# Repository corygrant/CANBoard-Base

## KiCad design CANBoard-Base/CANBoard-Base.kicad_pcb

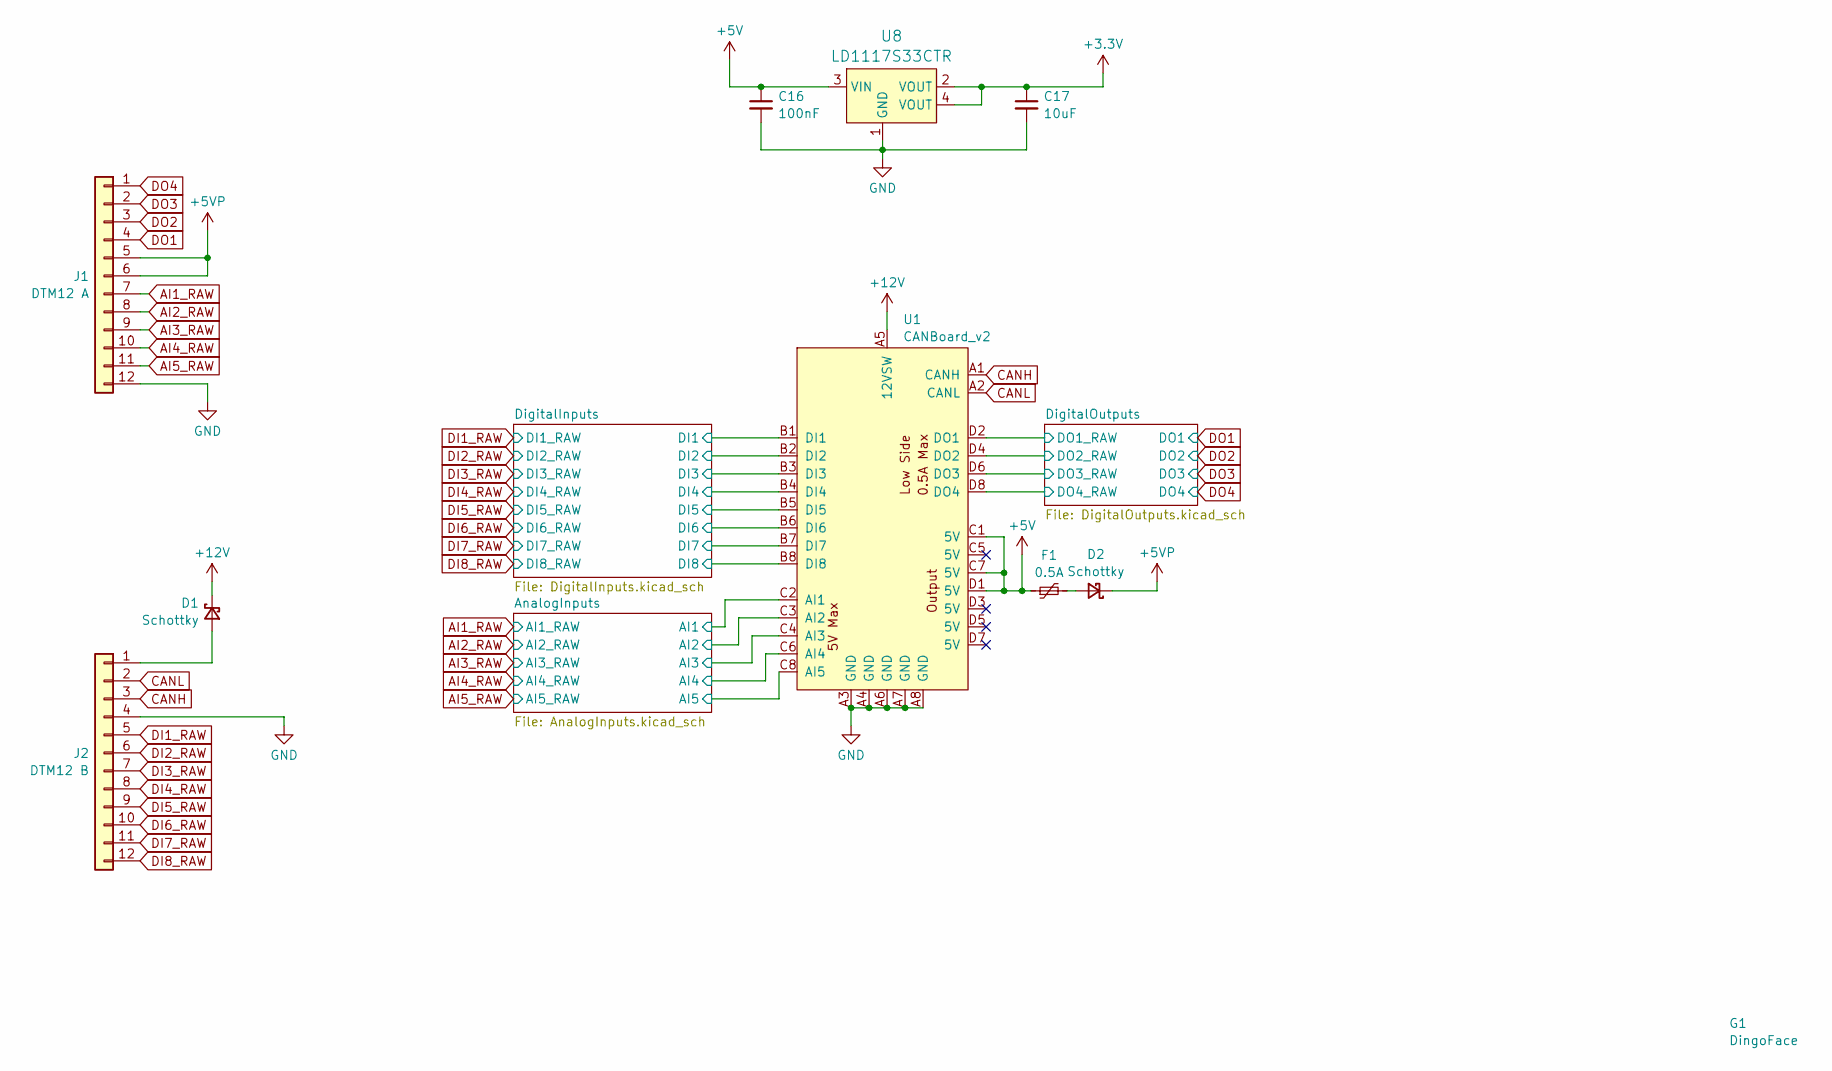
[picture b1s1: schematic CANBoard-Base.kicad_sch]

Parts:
C16: 100nF; C_0805_2012Metric; JLC_PN C49678
C17: 10uF; C_0805_2012Metric; JLC_PN C15850
D1, D2: Schottky; D_SOD-123; JLC_PN C179426
F1: 0.5A; Fuse_0805_2012Metric; JLC_PN C22378359
G1: DingoFace; DingoFaceNoFill
J1: DTM12 A; TE_DTM15-12Px_NoScrewHoles
J2: DTM12 B; TE_DTM15-12Px_NoScrewHoles
U1: CANBoard_v2; CANBoard_v2_NoMountingHoles_TagConnectHoles
U8: LD1117S33CTR; SOT-223; MPN LD1117S33CTR; Digi-Key_PN 497-1241-1-ND

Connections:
+3.3V: C17.1, U8.2 (VOUT), U8.4 (VOUT); also elsewhere on the board
+5V: C16.1, F1.1, U1.C1 (5V), U1.C7 (5V), U1.D1 (5V), U8.3 (VIN); also elsewhere on the board
+5VP: D2.1 (K), J1.5, J1.6
+12V: D1.1 (K), U1.A5 (12VSW); also elsewhere on the board
/AnalogInputs/AI1: U1.C2 (AI1); also elsewhere on the board
/AnalogInputs/AI2: U1.C3 (AI2); also elsewhere on the board
/AnalogInputs/AI3: U1.C4 (AI3); also elsewhere on the board
/AnalogInputs/AI4: U1.C6 (AI4); also elsewhere on the board
/AnalogInputs/AI5: U1.C8 (AI5); also elsewhere on the board
/DigitalInputs/DI1: U1.B1 (DI1); also elsewhere on the board
/DigitalInputs/DI2: U1.B2 (DI2); also elsewhere on the board
/DigitalInputs/DI3: U1.B3 (DI3); also elsewhere on the board
/DigitalInputs/DI4: U1.B4 (DI4); also elsewhere on the board
/DigitalInputs/DI5: U1.B5 (DI5); also elsewhere on the board
/DigitalInputs/DI6: U1.B6 (DI6); also elsewhere on the board
/DigitalInputs/DI7: U1.B7 (DI7); also elsewhere on the board
/DigitalInputs/DI8: U1.B8 (DI8); also elsewhere on the board
/DigitalOutputs/DO1_RAW: U1.D2 (DO1); also elsewhere on the board
/DigitalOutputs/DO2_RAW: U1.D4 (DO2); also elsewhere on the board
/DigitalOutputs/DO3_RAW: U1.D6 (DO3); also elsewhere on the board
/DigitalOutputs/DO4_RAW: U1.D8 (DO4); also elsewhere on the board
AI1_RAW: J1.7; also elsewhere on the board
AI2_RAW: J1.8; also elsewhere on the board
AI3_RAW: J1.9; also elsewhere on the board
AI4_RAW: J1.10; also elsewhere on the board
AI5_RAW: J1.11; also elsewhere on the board
CANH: J2.3, U1.A1 (CANH)
CANL: J2.2, U1.A2 (CANL)
DI1_RAW: J2.5; also elsewhere on the board
DI2_RAW: J2.6; also elsewhere on the board
DI3_RAW: J2.7; also elsewhere on the board
DI4_RAW: J2.8; also elsewhere on the board
DI5_RAW: J2.9; also elsewhere on the board
DI6_RAW: J2.10; also elsewhere on the board
DI7_RAW: J2.11; also elsewhere on the board
DI8_RAW: J2.12; also elsewhere on the board
DO1: J1.4; also elsewhere on the board
DO2: J1.3; also elsewhere on the board
DO3: J1.2; also elsewhere on the board
DO4: J1.1; also elsewhere on the board
GND: C16.2, C17.2, J1.12, J2.4, U1.A3 (GND), U1.A4 (GND), U1.A6 (GND), U1.A7 (GND), U1.A8 (GND), U8.1 (GND); also elsewhere on the board
unnamed: D1.2 (A), J2.1
unnamed: D2.2 (A), F1.2

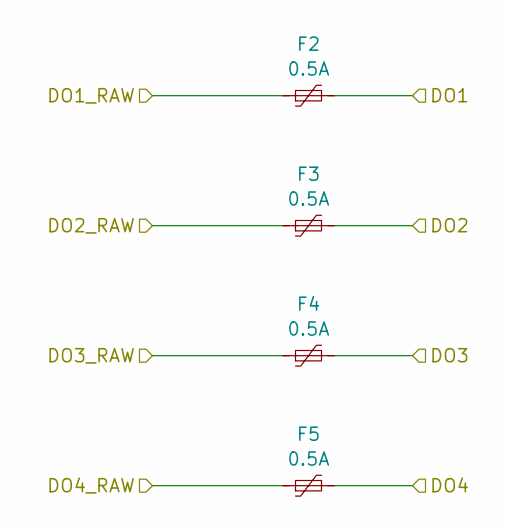
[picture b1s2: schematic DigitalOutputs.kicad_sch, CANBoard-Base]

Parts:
F2, F3, F4, F5: 0.5A; Fuse_0805_2012Metric; JLC_PN C22378359

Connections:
/DigitalOutputs/DO1_RAW: F2.1; also elsewhere on the board
/DigitalOutputs/DO2_RAW: F3.1; also elsewhere on the board
/DigitalOutputs/DO3_RAW: F4.1; also elsewhere on the board
/DigitalOutputs/DO4_RAW: F5.1; also elsewhere on the board
DO1: F2.2; also elsewhere on the board
DO2: F3.2; also elsewhere on the board
DO3: F4.2; also elsewhere on the board
DO4: F5.2; also elsewhere on the board

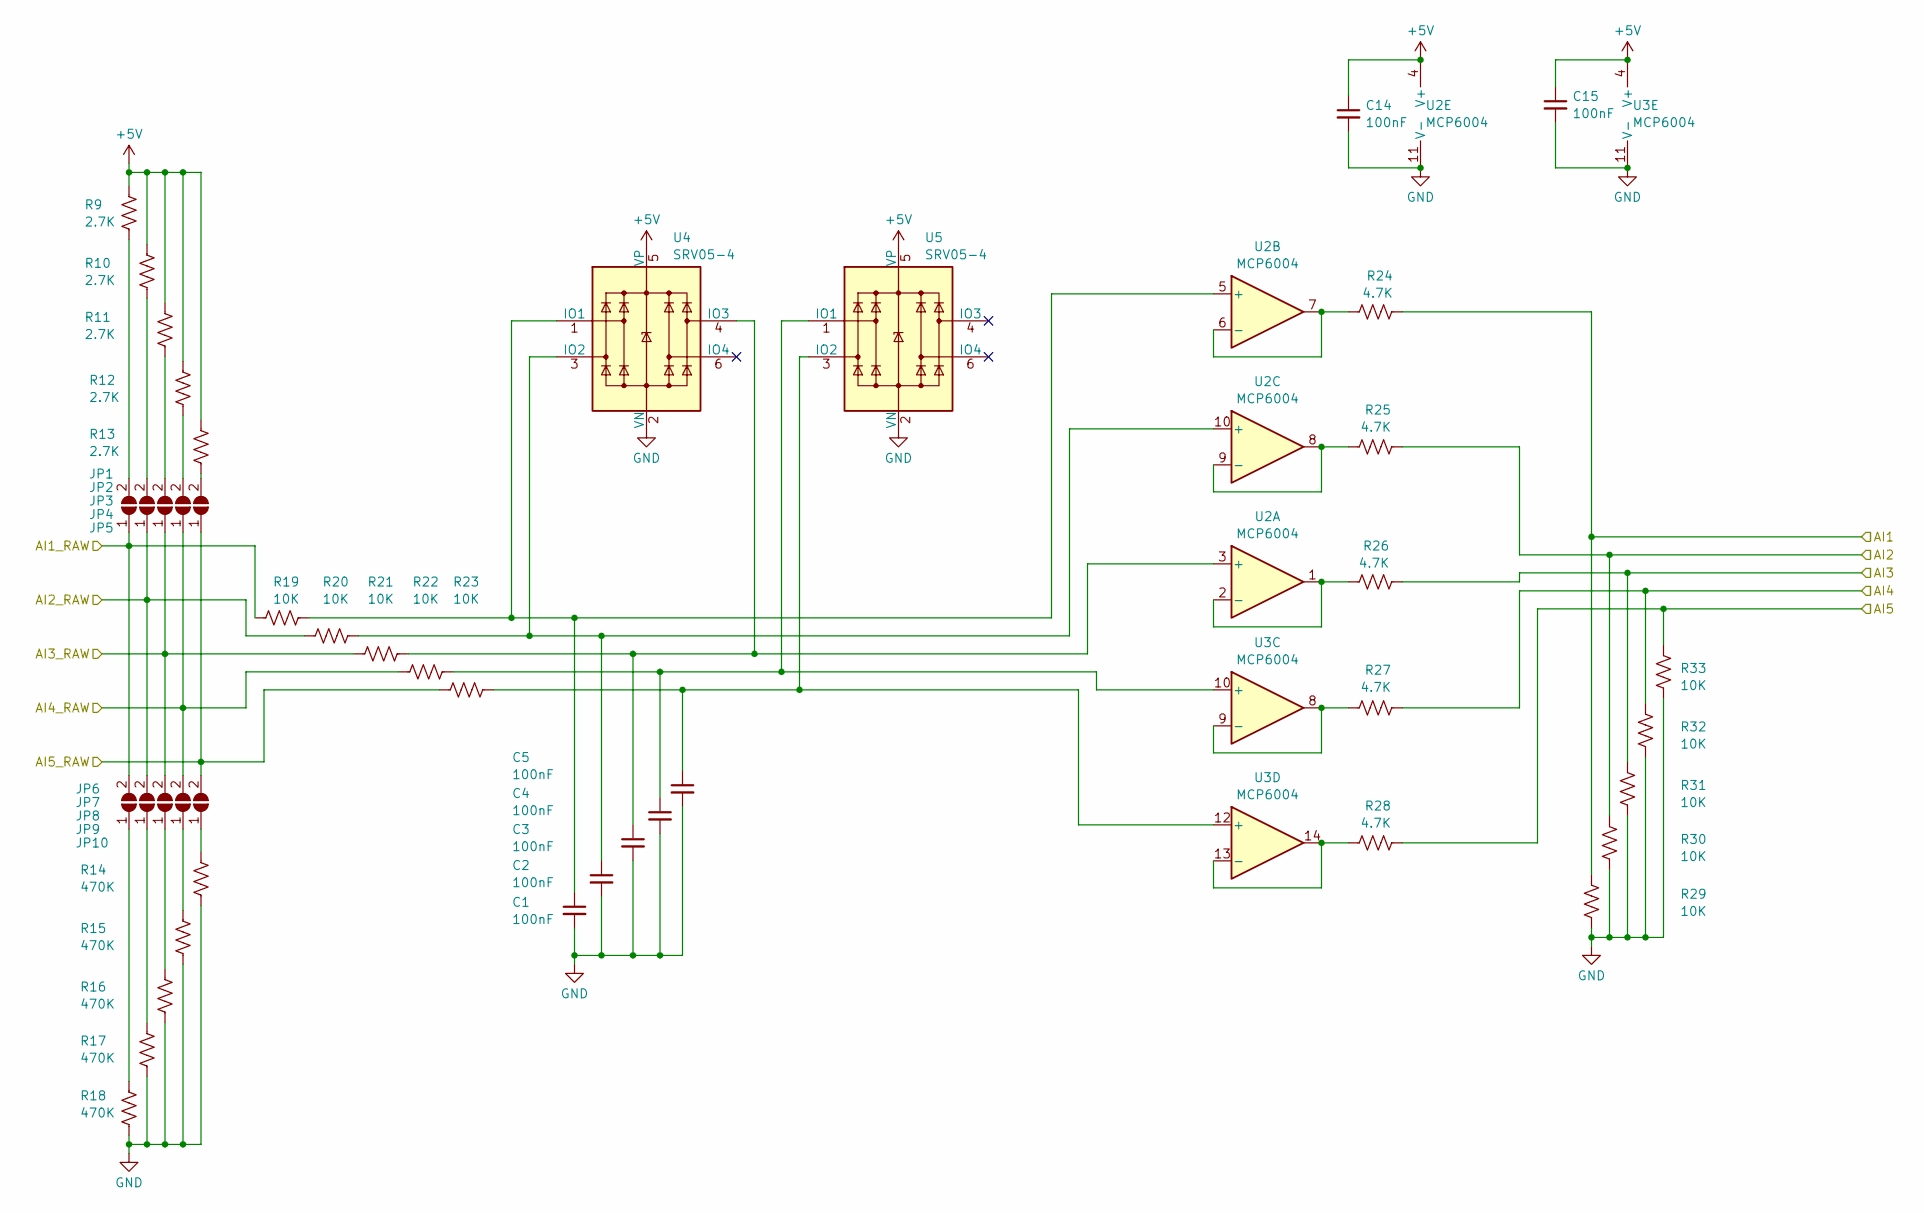
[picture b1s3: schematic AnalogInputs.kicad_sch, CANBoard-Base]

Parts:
C1, C2, C3, C4, C5, C14, C15: 100nF; C_0805_2012Metric; JLC_PN C49678
JP1, JP2, JP3, JP4, JP5, JP6, JP7, JP8, JP9, JP10: SolderJumper_2_Open; SolderJumper-2_P1.3mm_Open_RoundedPad1.0x1.5mm
R9, R10, R11, R12, R13: 2.7K; R_0805_2012Metric; JLC_PN C17530
R14, R15, R16, R17, R18: 470K; R_0805_2012Metric; JLC_PN C17709
R19, R20, R21, R22, R23, R29, R30, R31, R32, R33: 10K; R_0805_2012Metric; JLC_PN C17414
R24, R25, R26, R27, R28: 4.7K; R_0805_2012Metric; JLC_PN C17673
U2, U3: MCP6004; TSSOP-14_4.4x5mm_P0.65mm; JLC_PN C50282
U4, U5: SRV05-4; SOT-23-6; JLC_PN C384887

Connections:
+5V: C14.1, C15.1, R9.1, R10.1, R11.1, R12.1, R13.1, U2.4 (V+), U3.4 (V+), U4.5 (VP), U5.5 (VP); also elsewhere on the board
/AnalogInputs/AI1: R24.2, R29.1; also elsewhere on the board
/AnalogInputs/AI2: R25.2, R30.1; also elsewhere on the board
/AnalogInputs/AI3: R26.2, R31.1; also elsewhere on the board
/AnalogInputs/AI4: R27.2, R32.1; also elsewhere on the board
/AnalogInputs/AI5: R28.2, R33.1; also elsewhere on the board
AI1_RAW: JP1.1 (A), JP6.2 (B), R19.1; also elsewhere on the board
AI2_RAW: JP2.1 (A), JP7.2 (B), R20.1; also elsewhere on the board
AI3_RAW: JP3.1 (A), JP8.2 (B), R21.1; also elsewhere on the board
AI4_RAW: JP4.1 (A), JP9.2 (B), R22.1; also elsewhere on the board
AI5_RAW: JP5.1 (A), JP10.2 (B), R23.1; also elsewhere on the board
GND: C1.2, C2.2, C3.2, C4.2, C5.2, C14.2, C15.2, R14.2, R15.2, R16.2, R17.2, R18.2, R29.2, R30.2, R31.2, R32.2, R33.2, U2.11 (V-), U3.11 (V-), U4.2 (VN), U5.2 (VN); also elsewhere on the board
unnamed: JP1.2 (B), R9.2
unnamed: JP2.2 (B), R10.2
unnamed: JP3.2 (B), R11.2
unnamed: JP4.2 (B), R12.2
unnamed: JP5.2 (B), R13.2
unnamed: JP6.1 (A), R18.1
unnamed: JP7.1 (A), R17.1
unnamed: JP8.1 (A), R16.1
unnamed: JP9.1 (A), R15.1
unnamed: JP10.1 (A), R14.1
unnamed: C3.1, R21.2, U2.3 (+), U4.4 (IO3)
unnamed: R26.1, U2.1, U2.2 (-)
unnamed: C1.1, R19.2, U2.5 (+), U4.1 (IO1)
unnamed: R24.1, U2.6 (-), U2.7
unnamed: C2.1, R20.2, U2.10 (+), U4.3 (IO2)
unnamed: R25.1, U2.8, U2.9 (-)
unnamed: C4.1, R22.2, U3.10 (+), U5.1 (IO1)
unnamed: R27.1, U3.8, U3.9 (-)
unnamed: C5.1, R23.2, U3.12 (+), U5.3 (IO2)
unnamed: R28.1, U3.13 (-), U3.14

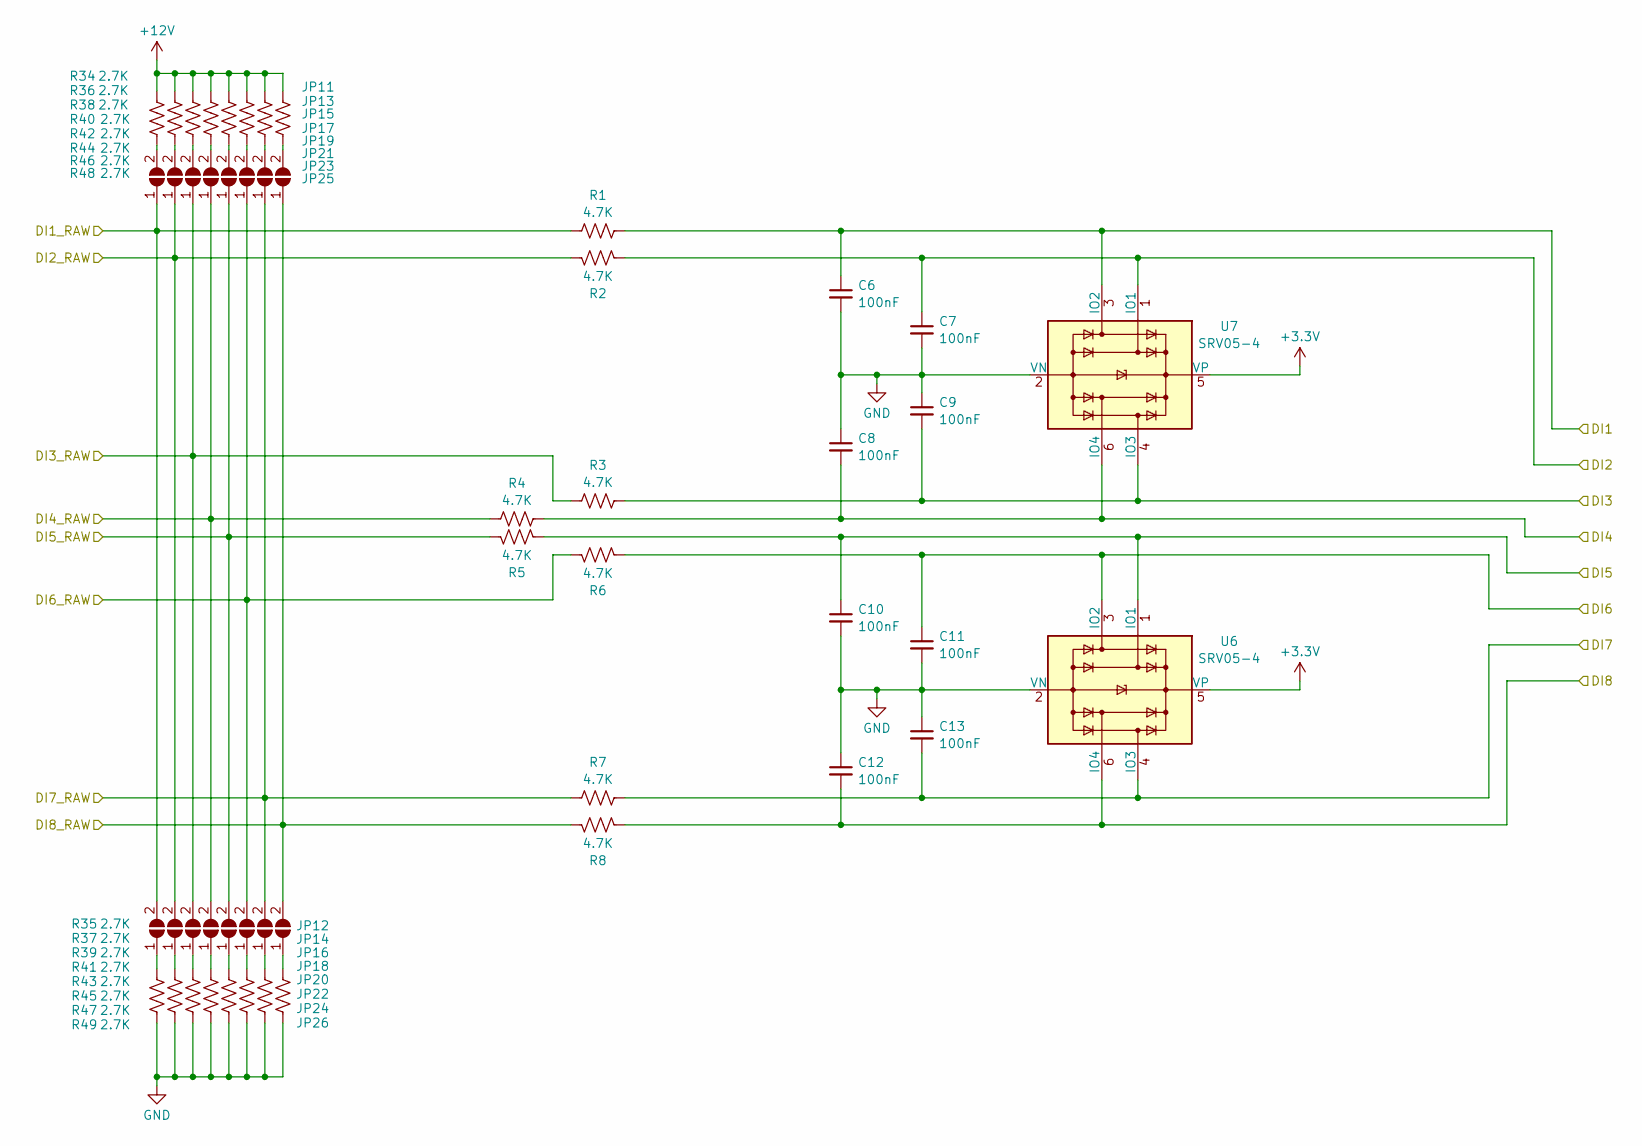
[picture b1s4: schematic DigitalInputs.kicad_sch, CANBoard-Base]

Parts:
C6, C7, C8, C9, C10, C11, C12, C13: 100nF; C_0805_2012Metric; JLC_PN C49678
JP11, JP12, JP13, JP14, JP15, JP16, JP17, JP18, JP19, JP20, JP21, JP22, JP23, JP24, JP25, JP26: SolderJumper_2_Open; SolderJumper-2_P1.3mm_Open_RoundedPad1.0x1.5mm
R1, R2, R3, R4, R5, R6, R7, R8: 4.7K; R_0805_2012Metric; JLC_PN C17673
R34, R35, R36, R37, R38, R39, R40, R41, R42, R43, R44, R45, R46, R47, R48, R49: 2.7K; R_0805_2012Metric; JLC_PN C17530
U6, U7: SRV05-4; SOT-23-6; JLC_PN C384887

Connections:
+3.3V: U6.5 (VP), U7.5 (VP); also elsewhere on the board
+12V: R34.1, R36.1, R38.1, R40.1, R42.1, R44.1, R46.1, R48.1; also elsewhere on the board
/DigitalInputs/DI1: C6.1, R1.2, U7.3 (IO2); also elsewhere on the board
/DigitalInputs/DI2: C7.1, R2.2, U7.1 (IO1); also elsewhere on the board
/DigitalInputs/DI3: C9.2, R3.2, U7.4 (IO3); also elsewhere on the board
/DigitalInputs/DI4: C8.2, R4.2, U7.6 (IO4); also elsewhere on the board
/DigitalInputs/DI5: C10.1, R5.2, U6.1 (IO1); also elsewhere on the board
/DigitalInputs/DI6: C11.1, R6.2, U6.3 (IO2); also elsewhere on the board
/DigitalInputs/DI7: C13.2, R7.2, U6.4 (IO3); also elsewhere on the board
/DigitalInputs/DI8: C12.2, R8.2, U6.6 (IO4); also elsewhere on the board
DI1_RAW: JP11.1 (A), JP12.2 (B), R1.1; also elsewhere on the board
DI2_RAW: JP13.1 (A), JP14.2 (B), R2.1; also elsewhere on the board
DI3_RAW: JP15.1 (A), JP16.2 (B), R3.1; also elsewhere on the board
DI4_RAW: JP17.1 (A), JP18.2 (B), R4.1; also elsewhere on the board
DI5_RAW: JP19.1 (A), JP20.2 (B), R5.1; also elsewhere on the board
DI6_RAW: JP21.1 (A), JP22.2 (B), R6.1; also elsewhere on the board
DI7_RAW: JP23.1 (A), JP24.2 (B), R7.1; also elsewhere on the board
DI8_RAW: JP25.1 (A), JP26.2 (B), R8.1; also elsewhere on the board
GND: C6.2, C7.2, C8.1, C9.1, C10.2, C11.2, C12.1, C13.1, R35.2, R37.2, R39.2, R41.2, R43.2, R45.2, R47.2, R49.2, U6.2 (VN), U7.2 (VN); also elsewhere on the board
unnamed: JP11.2 (B), R34.2
unnamed: JP12.1 (A), R35.1
unnamed: JP13.2 (B), R36.2
unnamed: JP14.1 (A), R37.1
unnamed: JP15.2 (B), R38.2
unnamed: JP16.1 (A), R39.1
unnamed: JP17.2 (B), R40.2
unnamed: JP18.1 (A), R41.1
unnamed: JP19.2 (B), R42.2
unnamed: JP20.1 (A), R43.1
unnamed: JP21.2 (B), R44.2
unnamed: JP22.1 (A), R45.1
unnamed: JP23.2 (B), R46.2
unnamed: JP24.1 (A), R47.1
unnamed: JP25.2 (B), R48.2
unnamed: JP26.1 (A), R49.1

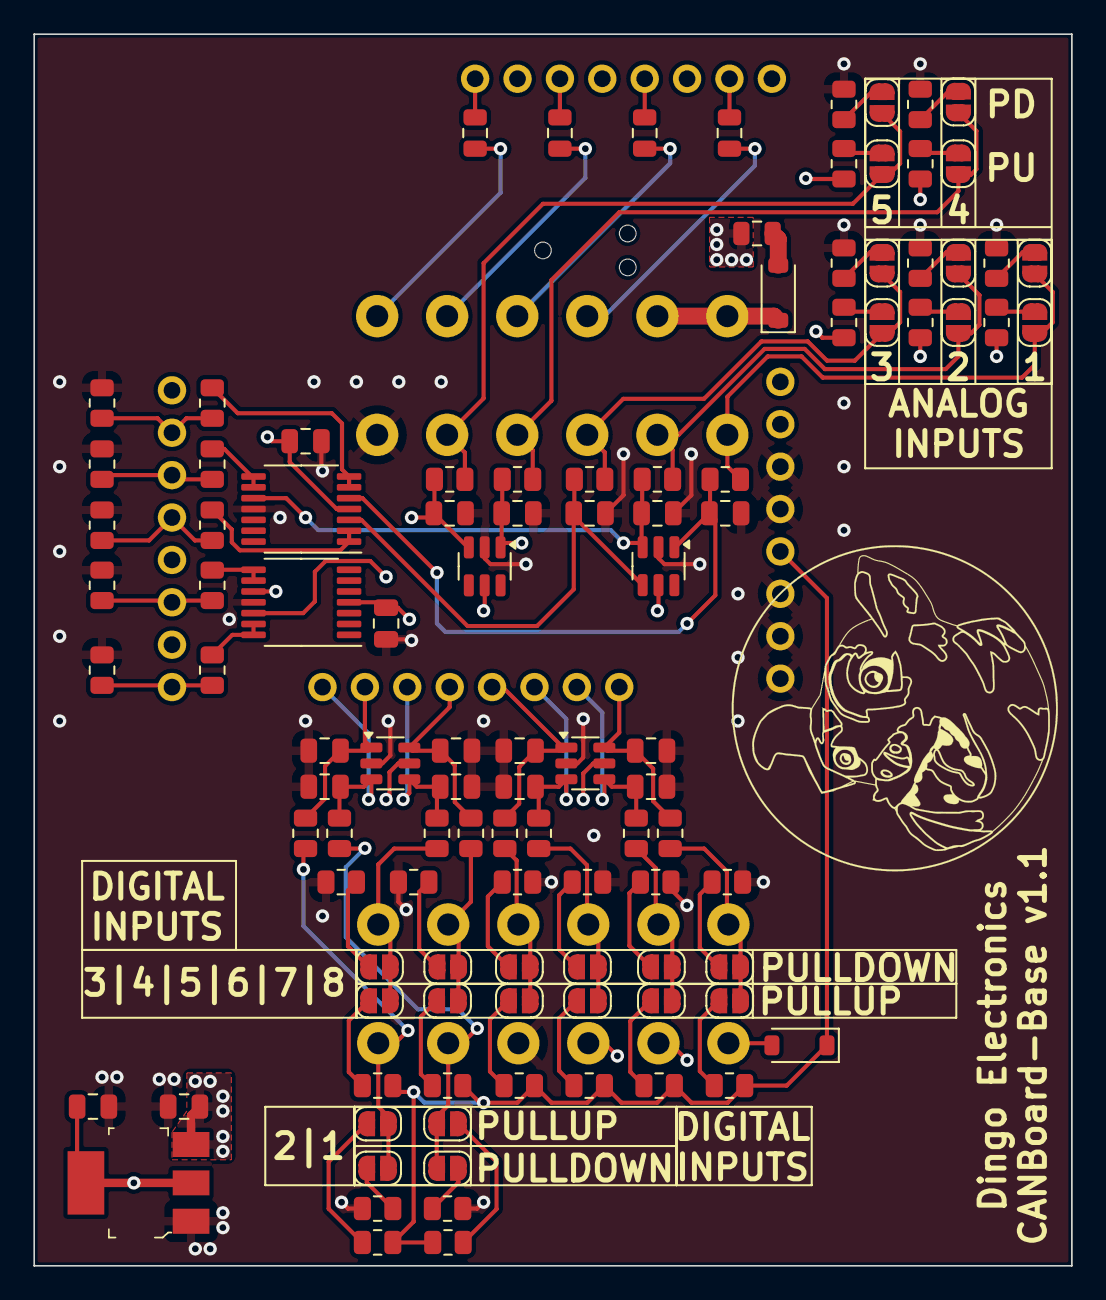
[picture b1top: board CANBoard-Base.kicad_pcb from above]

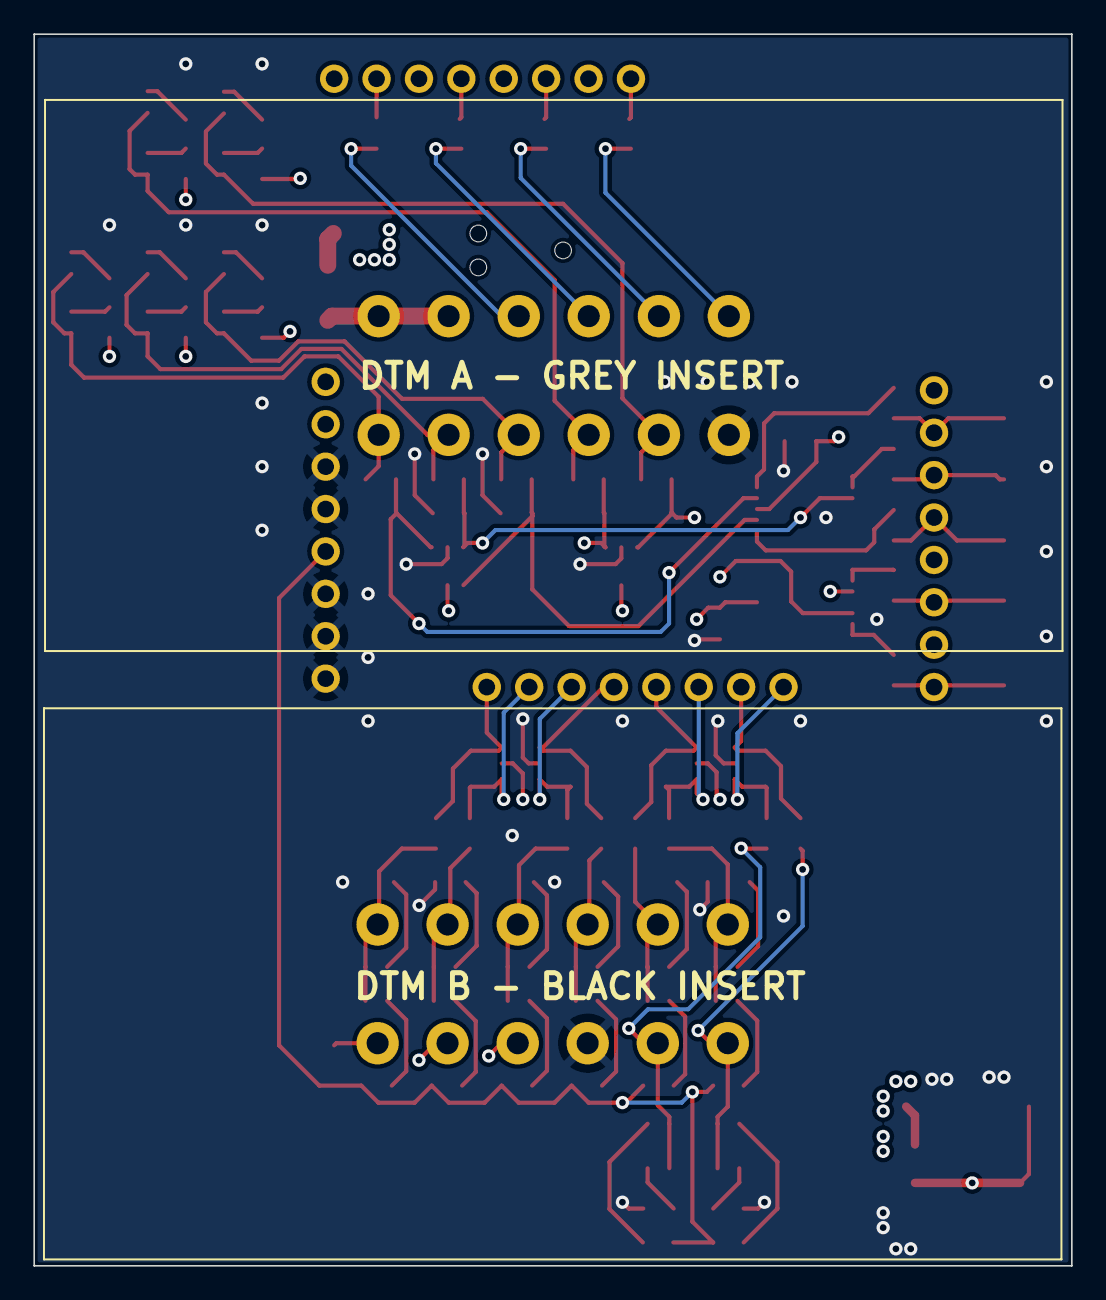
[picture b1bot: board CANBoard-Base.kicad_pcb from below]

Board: 4 copper layers, 62.2 x 73.8 mm, 110 parts (2 on the bottom side), 79 nets.

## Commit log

2024-07-14 Initial design
2024-07-14 Remove temp files
2024-07-18 Switched to v2
2024-09-06 Update to Kicad 8
2024-12-26 first layout complete
2024-12-27 as built v1
2024-12-27 update schem pdf
2024-12-27 add step file
2024-12-28 moved dtm connectors together
2024-12-28 updated pcb
2024-12-28 silkscreen changes
2024-12-29 add headers model
2025-01-18 version 1.1 ready for manuf
2025-01-19 change to mcp6004
2025-01-19 show canboard 3d
2025-01-23 added case
2025-01-24 fixed bad step export
